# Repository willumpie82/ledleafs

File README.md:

# ledleafs

Please note, this repo is shared as-is, no guarantees

a few attention points to the schematic and pcb that might need fixing
- check your LEDs, WS2812(RGB) vs SK6812(RGBWW), the footprint is 180deg rotated, no change in PCB needed just rotate the components (PCB desgin = WS2812)
- esp32C3 super micro doesn't want to boot when moounted with all pads (no clue why, nothing is connected except power and GPIO), I swapped it out for a Seeed-studio XAIO ESP32 with external antenna
- level shifter not assembled, just hot-wired GPIO of ESP directly to LED1
- no VEML (light sensor support in WLED)

parts used (non affiliate links)
- Conenctors: [https://vi.aliexpress.com/item/1005006028155508.html](https://vi.aliexpress.com/item/1005006028155508.html)https://vi.aliexpress.com/item/1005006028155508.html
- Switches: [https://vi.aliexpress.com/item/4001161324412.html](https://vi.aliexpress.com/item/4001161324412.html)https://vi.aliexpress.com/item/4001161324412.html
- LEDs: [https://vi.aliexpress.com/item/32641663497.html](https://vi.aliexpress.com/item/32641663497.html)https://vi.aliexpress.com/item/32641663497.html
- wires: [https://vi.aliexpress.com/item/1005006125634331.html](https://vi.aliexpress.com/item/1005006125634331.html)https://vi.aliexpress.com/item/1005006125634331.html

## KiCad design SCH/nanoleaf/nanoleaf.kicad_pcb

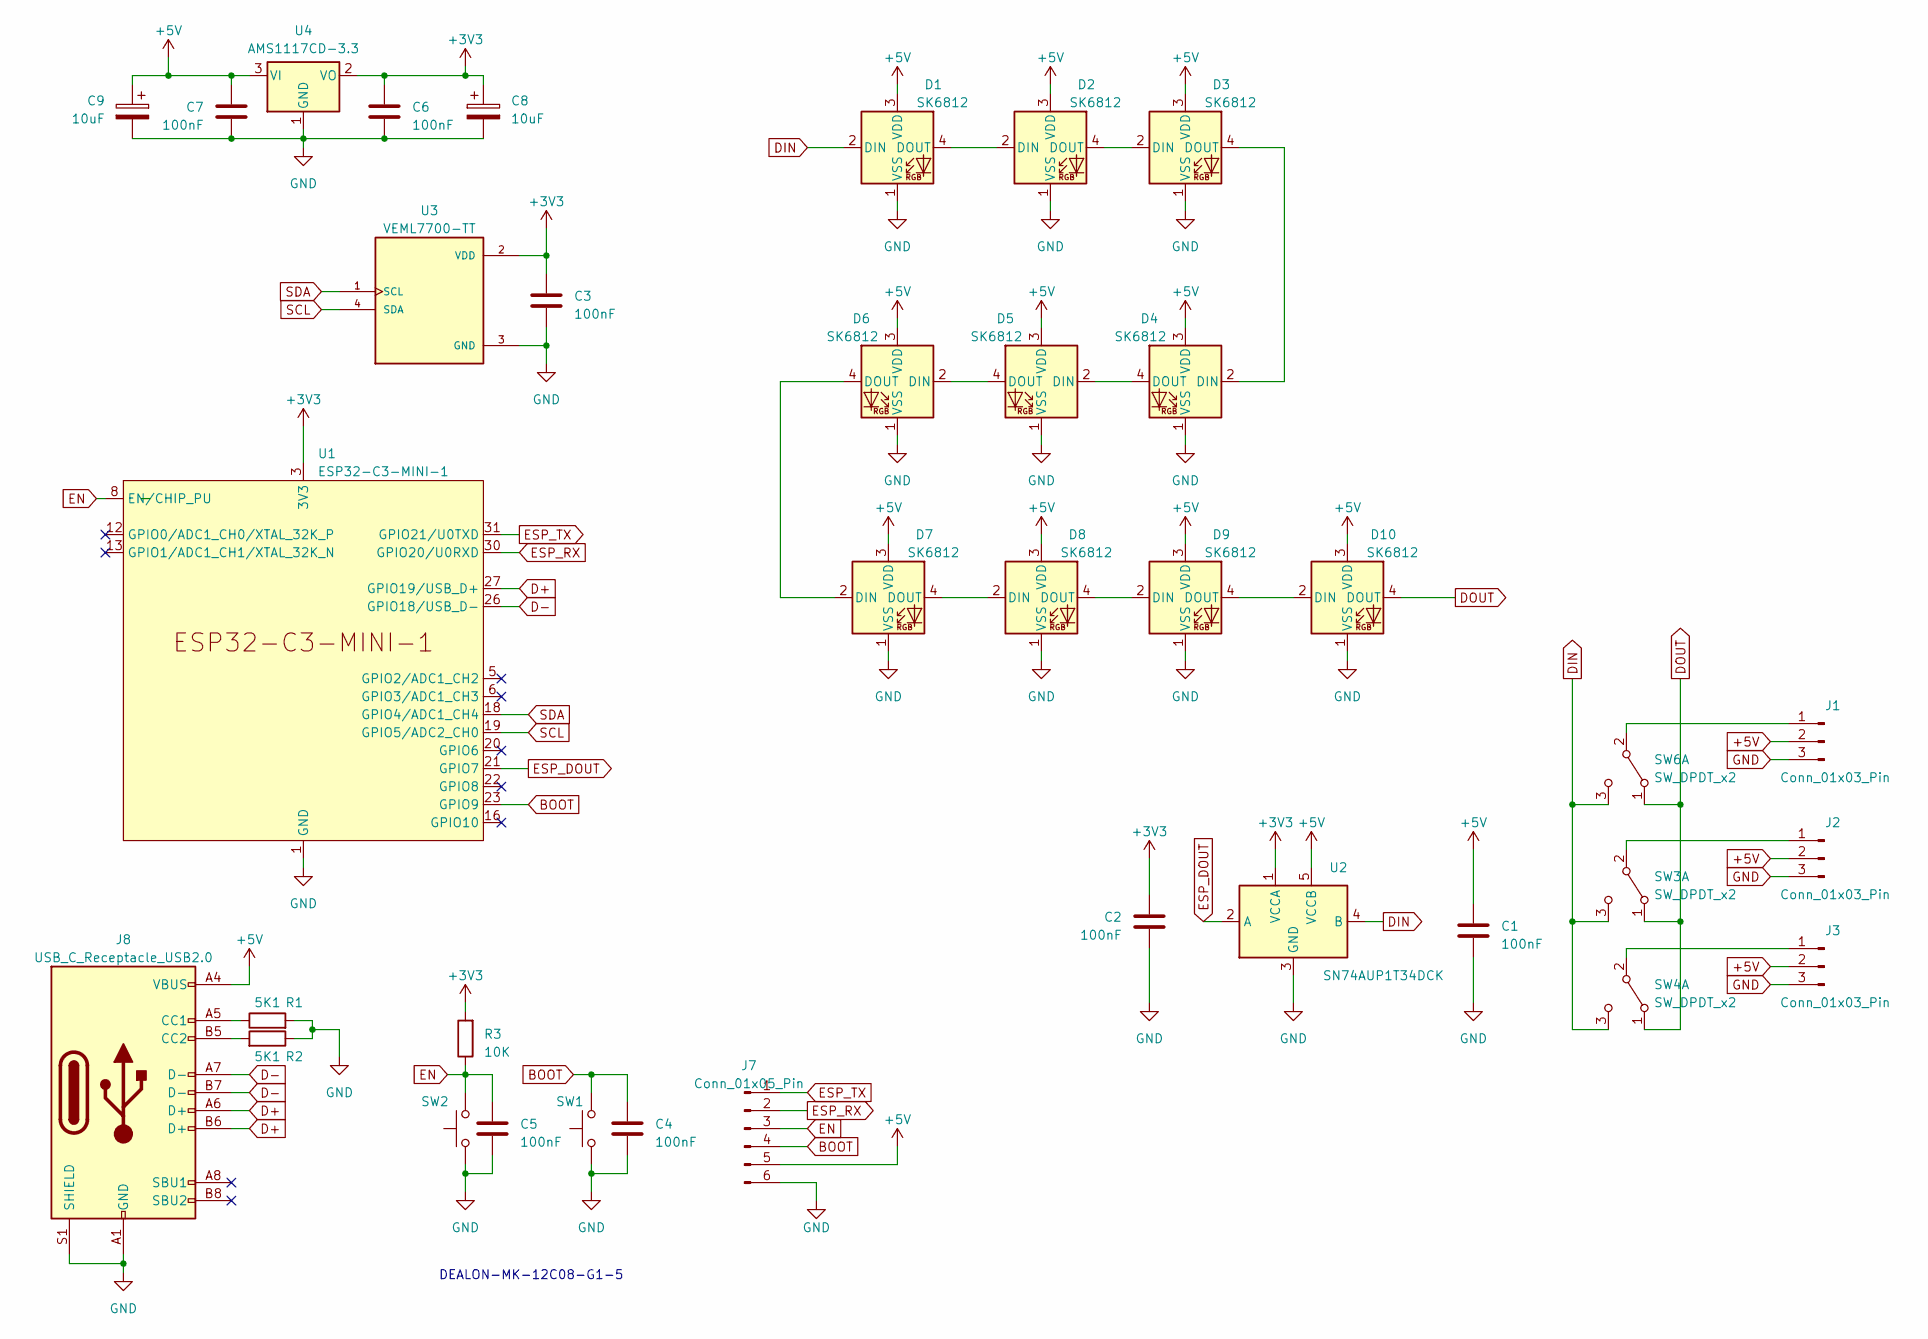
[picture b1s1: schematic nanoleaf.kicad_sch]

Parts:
C1, C2, C3, C4, C5, C6, C7: 100nF; C_0201_0603Metric
C8, C9: 10uF; C_Elec_3x5.4
D1, D2, D3, D4, D5, D6, D7, D8, D9, D10: SK6812; LED_SK6812_PLCC4_5.0x5.0mm_P3.2mm
J1, J2, J3: Conn_01x03_Pin; JST_GH_SM03B-GHS-TB_1x03-1MP_P1.25mm_Horizontal
J7: Conn_01x05_Pin; PinHeader_1x06_P2.54mm_Vertical
J8: USB_C_Receptacle_USB2.0; USB_C_Receptacle_HRO_TYPE-C-31-M-12
R1, R2: 5K1; R_0603_1608Metric
R3: 10K; R_0603_1608Metric
SW1, SW2: SW_Push; SW_SPST_B3U-1000P
SW3, SW4, SW6: SW_DPDT_x2; SW_DPDT_CK_JS202011JCQN
U1: ESP32-C3-MINI-1
U2: SN74AUP1T34DCK; SOT-353_SC-70-5
U3: VEML7700-TT; XDCR_VEML7700-TT; PARTREV 1.6
U4: AMS1117CD-3.3; TO-252-3_TabPin2

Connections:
+3V3: C2.1, C3.1, C6.1, C8.1, R3.2, U1.3 (3V3), U2.1 (VCCA), U3.2 (VDD), U4.2 (VO)
+5V: C1.1, C7.1, C9.1, D1.3 (VDD), D2.3 (VDD), D3.3 (VDD), D4.3 (VDD), D5.3 (VDD), D6.3 (VDD), D7.3 (VDD), D8.3 (VDD), D9.3 (VDD), D10.3 (VDD), J1.2, J2.2, J3.2, J7.5, J8.A4 (VBUS), J8.A9 (VBUS), J8.B4 (VBUS), J8.B9 (VBUS), U2.5 (VCCB), U4.3 (VI)
BOOT: C4.1, J7.4, SW1.2, U1.23 (GPIO9)
D+: J8.A6 (D+), J8.B6 (D+), U1.27 (GPIO19/USB_D+)
D-: J8.A7 (D-), J8.B7 (D-), U1.26 (GPIO18/USB_D-)
DIN: D1.2 (DIN), SW3.3 (C), SW4.3 (C), SW6.3 (C), U2.4 (B)
DOUT: D10.4 (DOUT), SW3.1 (A), SW4.1 (A), SW6.1 (A)
EN: C5.1, J7.3, R3.1, SW2.2, U1.8 (EN/CHIP_PU)
ESP_DOUT: U1.21 (GPIO7), U2.2 (A)
ESP_RX: J7.2, U1.30 (GPIO20/U0RXD)
ESP_TX: J7.1, U1.31 (GPIO21/U0TXD)
GND: C1.2, C2.2, C3.2, C4.2, C5.2, C6.2, C7.2, C8.2, C9.2, D1.1 (VSS), D2.1 (VSS), D3.1 (VSS), D4.1 (VSS), D5.1 (VSS), D6.1 (VSS), D7.1 (VSS), D8.1 (VSS), D9.1 (VSS), D10.1 (VSS), J1.3, J2.3, J3.3, J7.6, J8.A1 (GND), J8.A12 (GND), J8.B1 (GND), J8.B12 (GND), J8.S1 (SHIELD), R1.2, R2.1, SW1.1, SW2.1, U1.1 (GND), U1.2 (GND), U1.11 (GND), U1.14 (GND), U1.36 (GND), U1.37 (GND), U1.38 (GND), U1.39 (GND), U1.40 (GND), U1.41 (GND), U1.42 (GND), U1.43 (GND), U1.44 (GND), U1.45 (GND), U1.46 (GND), U1.47 (GND), U1.48 (GND), U1.49 (GND), U1.50 (GND), U1.51 (GND), U1.52 (GND), U1.53 (GND), U2.3 (GND), U3.3 (GND), U4.1 (GND)
unnamed: D1.4 (DOUT), D2.2 (DIN)
unnamed: D2.4 (DOUT), D3.2 (DIN)
unnamed: D3.4 (DOUT), D4.2 (DIN)
unnamed: D4.4 (DOUT), D5.2 (DIN)
unnamed: D5.4 (DOUT), D6.2 (DIN)
unnamed: D6.4 (DOUT), D7.2 (DIN)
unnamed: D7.4 (DOUT), D8.2 (DIN)
unnamed: D8.4 (DOUT), D9.2 (DIN)
unnamed: D9.4 (DOUT), D10.2 (DIN)
unnamed: J1.1, SW6.2 (B)
unnamed: J2.1, SW3.2 (B)
unnamed: J3.1, SW4.2 (B)
unnamed: J8.A5 (CC1), R1.1
unnamed: J8.B5 (CC2), R2.2
SCL: U1.19 (GPIO5/ADC2_CH0), U3.4 (SDA)
SDA: U1.18 (GPIO4/ADC1_CH4), U3.1 (SCL)

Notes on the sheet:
DEALON-MK-12C08-G1-5

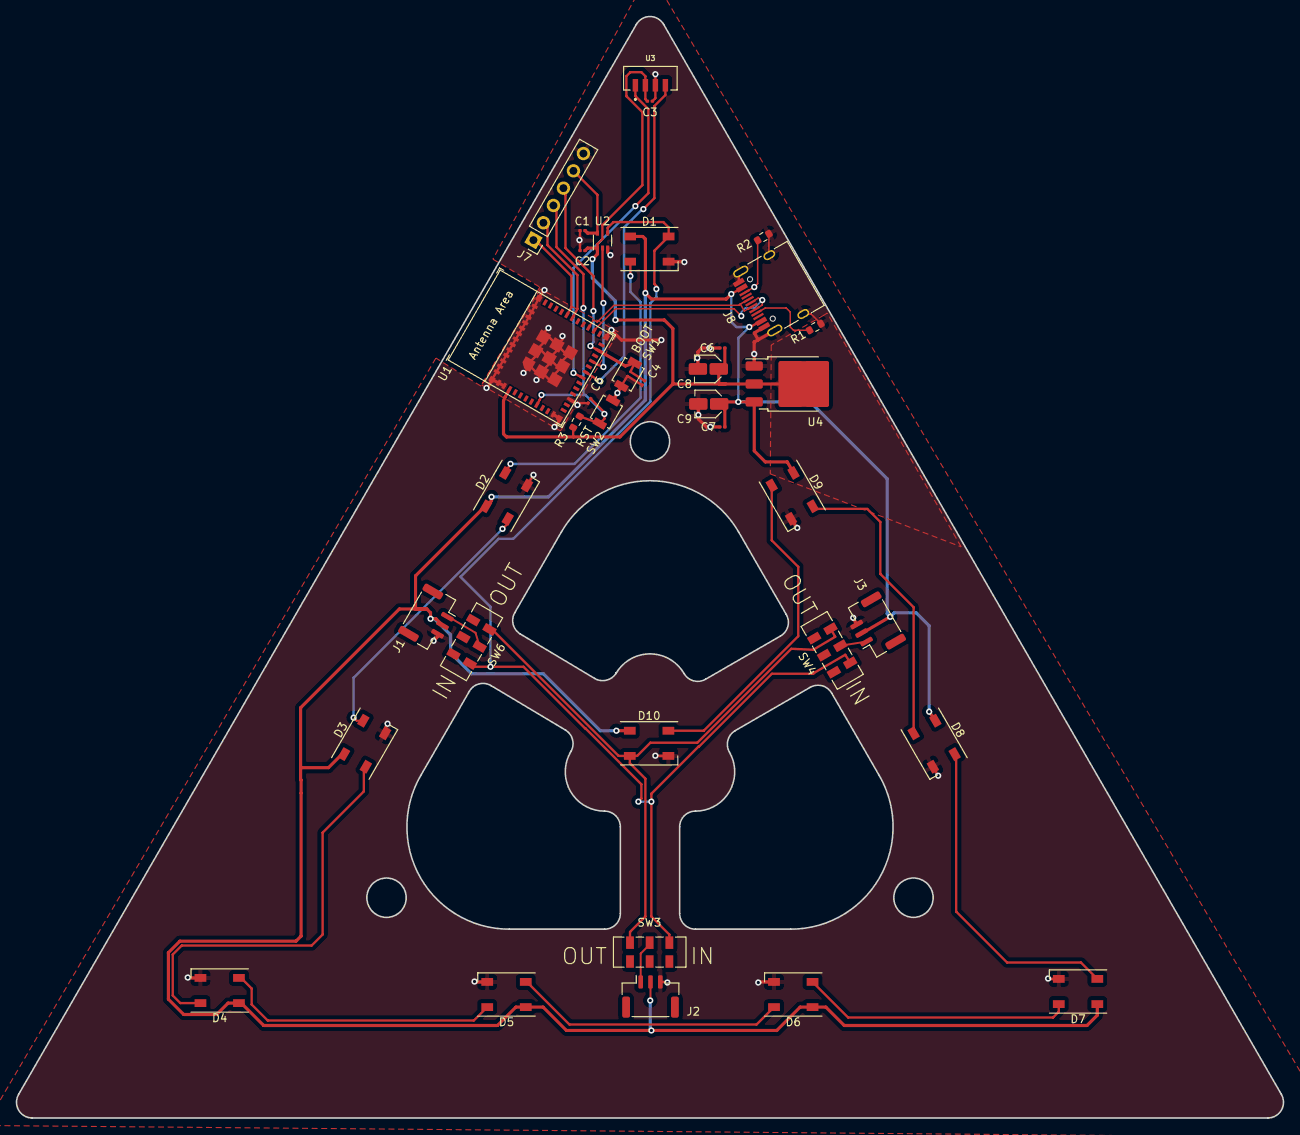
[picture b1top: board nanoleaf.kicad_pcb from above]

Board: 2 copper layers, 161.0 x 140.0 mm, 36 parts (0 on the bottom side), 28 nets.

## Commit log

2024-02-09 production files
2024-02-09 Add doc
2024-02-09 added gcode and stock
2024-02-09 switch and jst PH
2024-02-09 esp-c3-supermini
2024-02-09 update sch
